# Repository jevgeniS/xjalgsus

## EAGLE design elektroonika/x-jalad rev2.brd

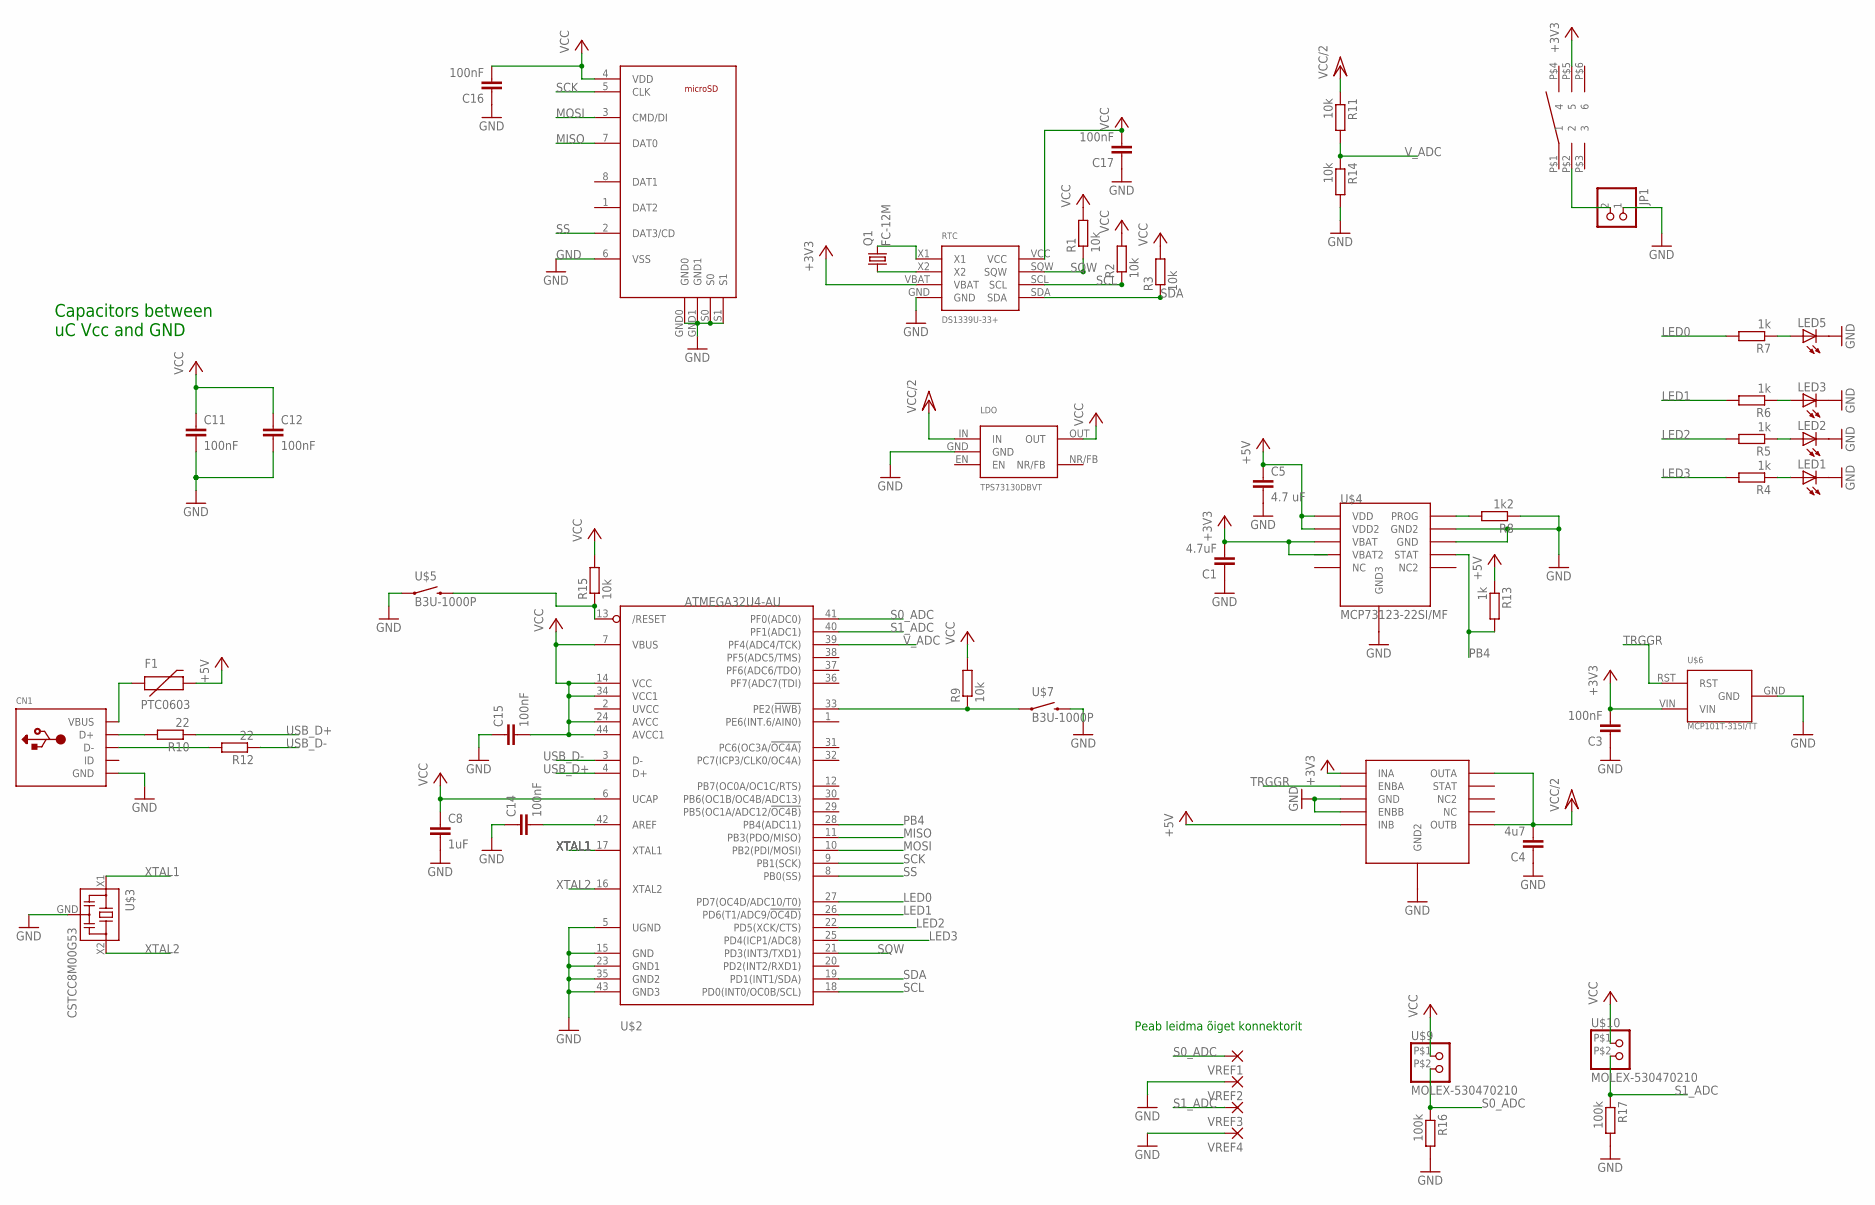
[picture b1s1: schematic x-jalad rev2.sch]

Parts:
2CH_IDEAL_DIODES: LTC4413EDD-1; DFN10
C1: 4.7uF; C0402
C3, C11, C12, C14, C15, C16, C17: 100nF; C0402
C4: 4u7; C0402
C5: 4.7 uF; C0603
C8: 1uF; C0402
CN1: USBMINIB; USB-MINIB
F1: PTC0603; 0603
JP1: PINHD-1X2/90; 1X02/90
LDO: TPS73130DBVT; SOT23-5
LED1, LED2, LED3, LED5: LEDLD260; LD260
Q1: FC-12M
R1, R2, R3, R9, R11, R14, R15: 10k; R0402
R4, R5, R6, R7, R13: 1k; R0402
R8: 1k2; R0402
R10, R12: 22; R0402
R16, R17: 100k; R0402
RTC: DS1339U-33+; MSOP8
U$1: MICROSD_HRS
U$2: ATMEGA32U4-AU; TQFP44
U$3: CSTCC8M00G53; SMDRESONATOR
U$4: MCP73123-22SI/MF; DFN10
U$5, U$7: B3U-1000P; SMD_BUTTON
U$6: MCP101T-315I/TT; SOT23-3
U$8: SPPH410100; SMD_LATCHING_BUTTON
U$9, U$10: MOLEX-530470210; SMD_PINHEADER
VREF1, VREF2, VREF3, VREF4: 3,17/1,3

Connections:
+5V: 2CH_IDEAL_DIODES.INB, C5.1, F1.2, R13.1, U$4.VDD, U$4.VDD2
GND: 2CH_IDEAL_DIODES.ENBB, 2CH_IDEAL_DIODES.GND, 2CH_IDEAL_DIODES.GND2, C1.1, C3.1, C4.1, C5.2, C8.2, C11.2, C12.2, C14.1, C15.1, C16.1, C17.1, CN1.GND, JP1.1, LDO.GND, LED1.K (C), LED2.K (C), LED3.K (C), LED5.K (C), R8.1, R14.2, R16.2, R17.2, RTC.GND, U$1.6 (VSS), U$1.GND0, U$1.GND1, U$1.S0, U$1.S1, U$2.5 (UGND), U$2.15 (GND), U$2.23 (GND1), U$2.35 (GND2), U$2.43 (GND3), U$3.GND, U$4.GND, U$4.GND2, U$4.GND3, U$5.P$1 (1), U$6.GND, U$7.P$2 (2), VREF2.1, VREF4.1
LED0: R7.2, U$2.27 (PD7(OC4D/ADC10/T0))
LED1: R6.2, U$2.26 (PD6(T1/ADC9/!OC4D))
LED2: R5.2, U$2.22 (PD5(XCK/CTS))
LED3: R4.2, U$2.25 (PD4(ICP1/ADC8))
MISO: U$1.7 (DAT0), U$2.11 (PB3(PDO/MISO))
MOSI: U$1.3 (CMD/DI), U$2.10 (PB2(PDI/MOSI))
unnamed: LED5.A, R7.1
unnamed: LED1.A, R4.1
unnamed: R8.2, U$4.PROG
unnamed: LED2.A, R5.1
unnamed: LED3.A, R6.1
unnamed: Q1.1, RTC.X2
unnamed: CN1.VBUS, F1.1
unnamed: CN1.D+, R10.2
unnamed: CN1.D-, R12.2
unnamed: Q1.2, RTC.X1
unnamed: C14.2, U$2.42 (AREF)
NRST: R15.1, U$2.13 (/RESET), U$5.P$2 (2)
NRST1: R9.1, U$2.33 (PE2(!HWB)), U$7.P$1 (1)
PB4: R13.2, U$2.28 (PB4(ADC11)), U$4.STAT
S0_ADC: R16.1, U$2.41 (PF0(ADC0)), U$9.P$2 (2), VREF1.1
S1_ADC: R17.1, U$2.40 (PF1(ADC1)), U$10.P$2 (2), VREF3.1
SCK: U$1.5 (CLK), U$2.9 (PB1(SCK))
SCL: R2.1, RTC.SCL, U$2.18 (PD0(INT0/OC0B/SCL))
SDA: R3.1, RTC.SDA, U$2.19 (PD1(INT1/SDA))
SQW: R1.1, RTC.SQW, U$2.21 (PD3(INT3/TXD1))
SS: U$1.2 (DAT3/CD), U$2.8 (PB0(SS))
TRGGR: 2CH_IDEAL_DIODES.ENBA, U$6.RST
USB_D+: R10.1, U$2.4 (D+)
USB_D-: R12.1, U$2.3 (D-)
VCC: C8.1, C11.1, C12.1, C15.2, C16.2, C17.2, LDO.OUT, R1.2, R2.2, R3.2, R9.2, R15.2, RTC.VCC, U$1.4 (VDD), U$2.6 (UCAP), U$2.7 (VBUS), U$2.14 (VCC), U$2.24 (AVCC), U$2.34 (VCC1), U$2.44 (AVCC1), U$9.P$1 (1), U$10.P$1 (1)
VCC/2: 2CH_IDEAL_DIODES.OUTA, 2CH_IDEAL_DIODES.OUTB, C4.2, LDO.IN, R11.1
V_ADC: R11.2, R14.1, U$2.39 (PF4(ADC4/TCK))
XTAL1: U$2.17 (XTAL1), U$3.X1
XTAL2: U$2.16 (XTAL2), U$3.X2

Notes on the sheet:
Capacitors between uC Vcc and GND
Peab leidma õiget konnektorit

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
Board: 2 copper layers, 48 parts (12 on the bottom side), 38 nets, no tracks yet.

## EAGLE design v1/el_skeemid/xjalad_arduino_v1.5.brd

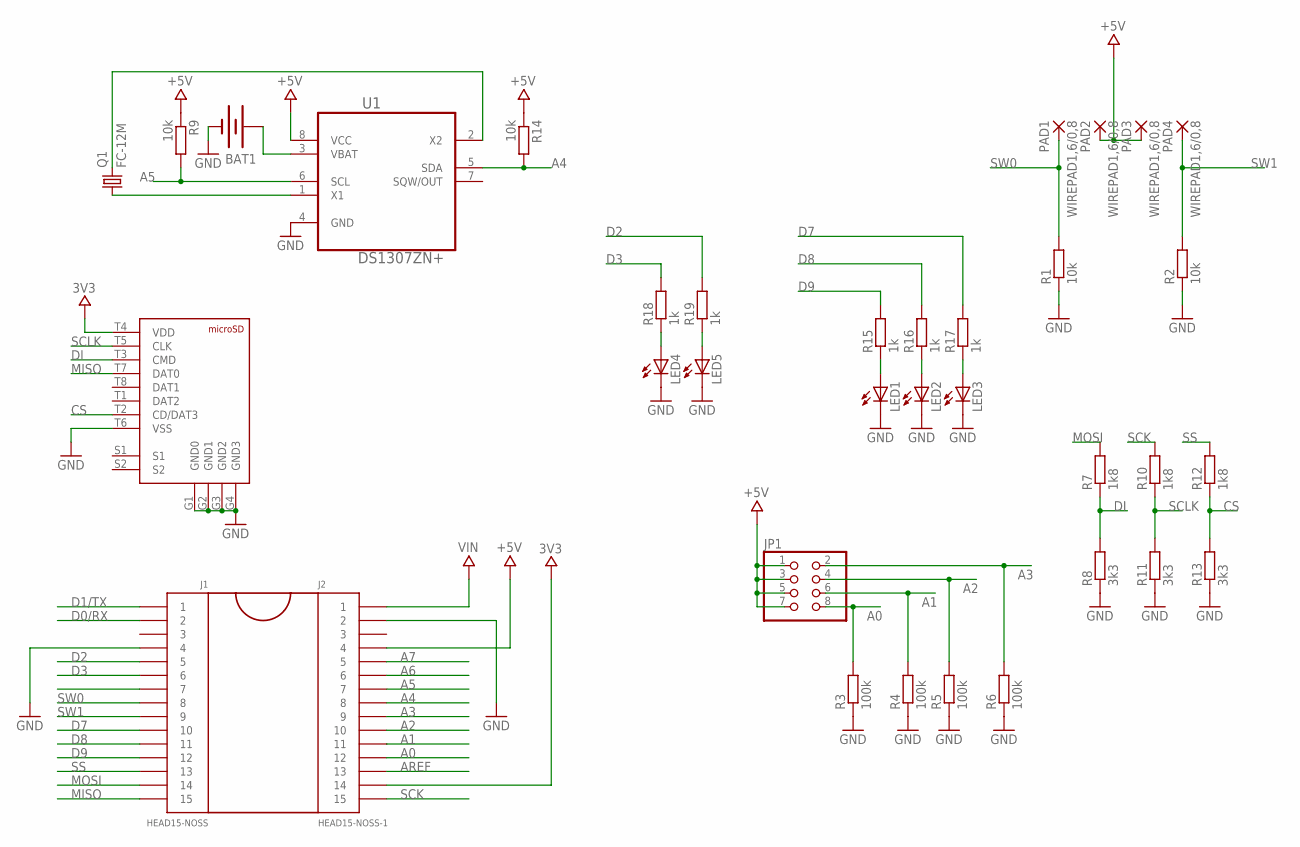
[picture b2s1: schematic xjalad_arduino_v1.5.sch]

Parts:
BAT1: BATTERY12MM; BATTCON_12MM
J1: HEAD15-NOSS
J2: HEAD15-NOSS-1
J3: MICROSD_MOLEX; MICROSD_104031
JP1: PINHD-2X4; 2X04
LED1, LED2, LED3, LED4, LED5: LED0603; LED-0603
PAD1, PAD2, PAD3, PAD4: WIREPAD1,6/0,8; 1,6/0,8
Q1: FC-12M
R1, R2, R9, R14: 10k; R0603
R3, R4, R5, R6: 100k; R0603
R7, R10, R12: 1k8; R0603
R8, R11, R13: 3k3; R0603
R15, R16, R17, R18, R19: 1k; R0603
U1: DS1307ZN+; SOIC127P600X175-8N

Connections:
3V3: J2.14, J3.T4 (VDD)
+5V: J2.4, JP1.1, JP1.3, JP1.5, JP1.7, PAD2.1, PAD3.1, R9.1, R14.1, U1.8 (VCC)
A0: J2.12, JP1.8, R3.2
A1: J2.11, JP1.6, R4.2
A2: J2.10, JP1.4, R5.2
A3: J2.9, JP1.2, R6.2
A4: J2.8, R14.2, U1.5 (SDA)
A5: J2.7, R9.2, U1.6 (SCL)
A6: J2.6
A7: J2.5
AREF: J2.13
CS: J3.T2 (CD/DAT3), R12.1, R13.2
D0/RX: J1.2
D1/TX: J1.1
D2: J1.5, R19.2
D3: J1.6, R18.2
D7: J1.10, R17.2
D8: J1.11, R16.2
D9: J1.12, R15.2
DI: J3.T3 (CMD), R7.1, R8.2
GND: BAT1.GND (-), J1.4, J2.2, J3.G1 (GND0), J3.G2 (GND1), J3.G3 (GND2), J3.G4 (GND3), J3.T6 (VSS), LED1.C, LED2.C, LED3.C, LED4.C, LED5.C, R1.1, R2.1, R3.1, R4.1, R5.1, R6.1, R8.1, R11.1, R13.1, U1.4 (GND)
MISO: J1.15, J3.T7 (DAT0)
MOSI: J1.14, R7.2
unnamed: Q1.1, U1.1 (X1)
unnamed: Q1.2, U1.2 (X2)
unnamed: LED1.A, R15.1
unnamed: BAT1.PWR@1 (+), U1.3 (VBAT)
unnamed: LED2.A, R16.1
unnamed: LED3.A, R17.1
unnamed: LED4.A, R18.1
unnamed: LED5.A, R19.1
SCK: J2.15, R10.2
SCLK: J3.T5 (CLK), R10.1, R11.2
SS: J1.13, R12.2
SW0: J1.8, PAD1.1, R1.2
SW1: J1.9, PAD4.1, R2.2
VIN: J2.1

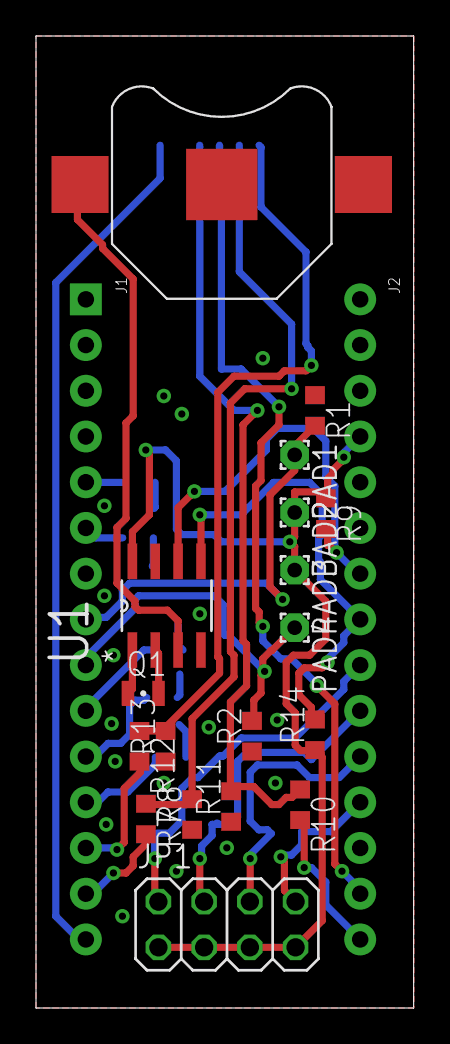
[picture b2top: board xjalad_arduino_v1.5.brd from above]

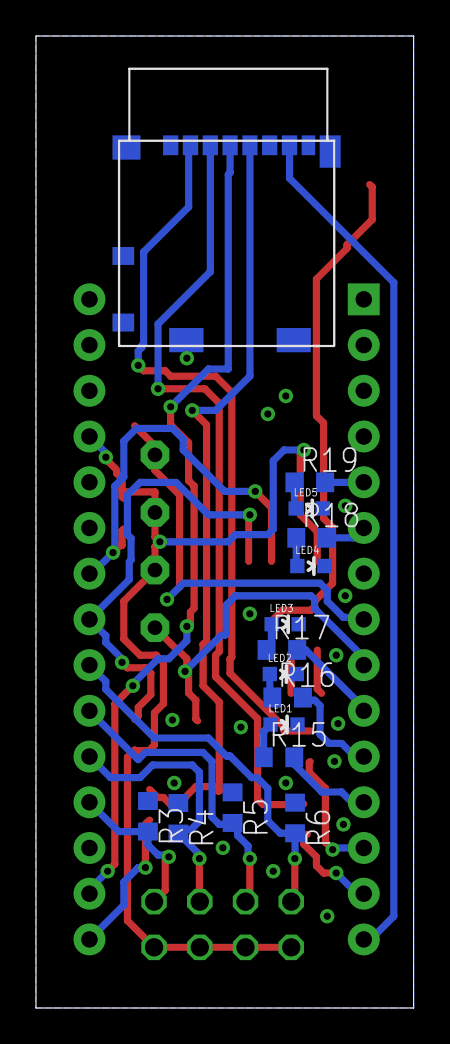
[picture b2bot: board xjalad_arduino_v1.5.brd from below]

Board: 2 copper layers, 21.0 x 54.0 mm, 35 parts (15 on the bottom side), 31 nets.

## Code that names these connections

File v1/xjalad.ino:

#include <SD.h>
#include "Wire.h"
#include <avr/interrupt.h>
#include <avr/power.h>
#include <avr/sleep.h>

#define DS1307_I2C_ADDRESS 0x68


#define LED0 2 //RED
#define LED1 3 //BLUE
#define LED2 7
#define LED3 8
#define LED4 9

#define CS 10
#define SW0_0 4
#define SW0_1 5
#define SW1_0 A6
#define SW1_1 A7
#define FSR0 A2 


#define MAX 0.8
#define MIN 0.2
//second -15624
//200 Hz - 3125
#define TIMER1_PERIOD 78
#define WFREQ 200 //Hz
#define WLAST 5
#define N 200*5

const int periods[3]={5,15,60};
byte chosenPeriod=5;
byte seconds=0;
int msecs=0;
volatile int n=0;
volatile boolean needToMeasure =true;
boolean samplesReady = false;
float tempSum;
Sd2Card card;
SdVolume volume;
SdFile root;
File myFile;
// month+day+hour+minute
char fileName[13];

// Convert binary coded decimal to normal decimal numbers
byte bcdToDec(byte val)
{
  return ( (val/16*10) + (val%16) );
}




String parseDateTimeValue(byte n){
  if (n<10)
    return ("0"+String(n, DEC));
  return String(n, DEC);
}


// Gets the date and time from the ds1307
void getDateDs1307(byte *second,
          byte *minute,
          byte *hour,
          byte *dayOfWeek,
          byte *dayOfMonth,
          byte *month,
          byte *year)
{
  // Reset the register pointer
  Wire.beginTransmission(DS1307_I2C_ADDRESS);
  Wire.write(0);
  Wire.endTransmission();
  
  Wire.requestFrom(DS1307_I2C_ADDRESS, 7);

  // A few of these need masks because certain bits are control bits
  *second     = bcdToDec(Wire.read() & 0x7f);
  *minute     = bcdToDec(Wire.read());
  *hour       = bcdToDec(Wire.read() & 0x3f);  // Need to change this if 12 hour am/pm
  *dayOfWeek  = bcdToDec(Wire.read());
  *dayOfMonth = bcdToDec(Wire.read());
  *month      = bcdToDec(Wire.read());
  *year       = bcdToDec(Wire.read());
}

String getTimeStamp(void){
  byte second, minute, hour, dayOfWeek, dayOfMonth, month, year;
  getDateDs1307(&second, &minute, &hour, &dayOfWeek, &dayOfMonth, &month, &year);
 
  return (parseDateTimeValue(hour)+":"+parseDateTimeValue(minute)+":"+parseDateTimeValue(second)+"  "+parseDateTimeValue(dayOfMonth)+"/"+parseDateTimeValue(month)+"/"+parseDateTimeValue(year));
}

String getTimeStampForFileName(void){
  byte second, minute, hour, dayOfWeek, dayOfMonth, month, year;
  getDateDs1307(&second, &minute, &hour, &dayOfWeek, &dayOfMonth, &month, &year);
 
  return (parseDateTimeValue(month)+parseDateTimeValue(dayOfMonth)+parseDateTimeValue(hour)+parseDateTimeValue(minute)) ;
}

boolean cardSetup(void){

  pinMode(CS, OUTPUT);     // change this to 53 on a mega
  // we'll use the initialization code from the utility libraries
  // since we're just testing if the card is working!
  if (!card.init(SPI_HALF_SPEED, CS)) {
    Serial.println("initialization failed. Things to check:");
    Serial.println("* is a card is inserted?");
    Serial.println("* Is your wiring correct?");
    Serial.println("* did you change the chipSelect pin to match your shield or module?");
    return false;
  } else {
   Serial.println("Wiring is correct and a card is present."); 
  }
  
  if (!SD.begin()) {
    Serial.println("initialization failed!");

  }
  Serial.println("initialization done.");
  
  // Now we will try to open the 'volume'/'partition' - it should be FAT16 or FAT32
  if (!volume.init(card)) {
    Serial.println("Could not find FAT16/FAT32 partition.\nMake sure you've formatted the card");
    return false;
  }
  root.openRoot(volume);
  return true;
}

void pinSetup(void){
  pinMode(SW1_0, INPUT);           // set pin to input
  pinMode(SW1_1, INPUT);           // set pin to input
  pinMode(FSR0,INPUT);
  
  //digitalWrite(pin, HIGH);       // turn on pullup resistors
}

byte readFreqSwitch(void){
  if (analogRead(SW1_0)>1022) return 0;
  if (analogRead(SW1_1)>1022) return 2;
  return 1;
} 

byte readModeSwitch(void){
  if (digitalRead(SW0_0)) return 0;
  if (digitalRead(SW0_1)) return 2;
  return 1;
}

float readSensor(byte n){
  
  switch (n){
    case 0: return analogRead(FSR0)/1023.0; break;
    case 1: return analogRead(FSR0)/1023.0; break;
    case 2: return analogRead(FSR0)/1023.0; break;
    case 3: return analogRead(FSR0)/1023.0; break;
  }
  //WARNING
  return -1;
}

String processSamples(){
  char buf [7];
  float average=tempSum/n;
  
  digitalWrite(LED2,LOW);
  digitalWrite(LED3,LOW);
  digitalWrite(LED4,LOW);
  
  if (average>MAX)
    digitalWrite(LED2,HIGH);
  else if (average<MIN)
    digitalWrite(LED4,HIGH);
  else
    digitalWrite(LED3,HIGH);

  dtostrf(average,1,3,buf);
  return (buf);
}

boolean createFile(){
  /*
  byte findex=1;
  while (true){
    if (!SD.exists("s.txt"))
      break;
    findex++;
  }
  */
  (String(getTimeStampForFileName()+".txt")).toCharArray(fileName,13);
  //fileName=getTimeStampForFileName();
  myFile=SD.open(fileName,FILE_WRITE);

  
  return true;
   
}

void configureInterrupt(int CV){
  cli();
  //set timer1 interrupt at 1Hz
  TCCR1A = 0;// set entire TCCR1A register to 0
  TCCR1B = 0;// same for TCCR1B
  TCNT1  = 0;//initialize counter value to 0
  // set compare match register for 1hz increments
  OCR1A = CV;// = (16*10^6) / (1*1024) - 1 (must be <65536)
  // turn on CTC mode
  TCCR1B |= (1 << WGM12);
  // Set CS10 and CS12 bits for 1024 prescaler
  // TIMER1_PRESCALER
  TCCR1B |= (1 << CS12) | (1 << CS10);  
  // enable timer compare interrupt
  TIMSK1 |= (1 << OCIE1A);
  sei();
}


void setup(void){
  Wire.begin();
  Serial.begin(9600);
 
  //setDateDs1307(15, 25, 16, 1, 22, 7, 13);
  Serial.println("Started!");
  
}


ISR(TIMER1_COMPA_vect){
  //Serial.println("second");
  
  if ((msecs+=5)>=1000) {
    seconds++;
    msecs=0;
  }
  
  if (needToMeasure){
    if (n<N){
      tempSum+=readSensor(0);
      n++;
    }
    else {
      samplesReady=true;
      needToMeasure=false;
      Serial.println("Samples ready");
    }
  }
   
  if (seconds>=chosenPeriod){
    seconds=0;
    msecs=0;
    n=0;
    tempSum=0;
    needToMeasure=true;
   // myFile.println(getTimeStamp()+' '+measure());
    
  }
  
}

void loop(void) {
 
  
  //Serial print mode
  
  if (readModeSwitch()==0){
    digitalWrite(LED1,HIGH);
    
    while (readModeSwitch()==0){
      char buf [7];
      String s=getTimeStamp()+' '+processSamples();
      //dtostrf(readSensor(0),1,3,buf);
      
       Serial.println(s);
       delay(500);
    }
    
    digitalWrite(LED1,LOW);
  }
  // Mem Card Store Mode
  if (readModeSwitch()==2){
     
    if (cardSetup() && createFile()){
     digitalWrite(LED0,HIGH);//RED
    chosenPeriod=15;//periods[readFreqSwitch()];
    seconds=0;
    msecs=0;
    n=0;
    needToMeasure=true;
    samplesReady=false;
    configureInterrupt(TIMER1_PERIOD);
    Serial.println("Mem Card start");
    while (readModeSwitch()==2){
      
       //Serial.println(measure());
       if (samplesReady){
         samplesReady=false;
         String s=getTimeStamp()+' '+processSamples();
         myFile=SD.open(fileName,FILE_WRITE);
         Serial.println(fileName);
         if (myFile){
           myFile.println(s);
           myFile.close();
           Serial.println(s);
         }
         else 
           Serial.println("Opening file failed");
         
       }
       //sleep()
       
       set_sleep_mode(SLEEP_MODE_PWR_SAVE);
        
        sleep_enable();
        sleep_mode();
        /* wake up here */
        sleep_disable();
       
    }
    
    digitalWrite(LED0,LOW);
    }
  }  
  
}

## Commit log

2013-12-10 initial
2013-12-10 initial v2
2013-12-13 LabView changed
2013-12-16 LV peaprogramm changed
2013-12-16 LabView changed and executables added
2013-12-16 arduino code changed
2013-12-16 LV and exe changed
2013-12-16 MainProgram exe added
2013-12-16 LV mainProgram changed to enable save after graph
2013-12-16 LV + exe + arduino
2013-12-17 eagle files init
2013-12-17 eagle files modified to fixed version made onboard
2014-02-16 fixed bug in realTimeMeasure and SetAttributes
2014-02-21 128 Hz measurements restored
2014-02-21 printing to serial row by row
2014-02-21 storing period 15 minutes added (not checked)
2014-02-21 time fixed
2014-02-21 bug fixes for final release
2014-06-18 peaprogramm fixes
2015-01-20 labview + arduino update
2015-01-21 Updated force calculation to match new sensors
2015-02-20 hot-fix for min and max levels, as they are sometimes loaded wrongly form EEPROM, should investigate further..

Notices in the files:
parts and their libraries:
SparkFun: Licensing: CC v3.0 Share-Alike You are welcome to use this library for commercial purposes.
